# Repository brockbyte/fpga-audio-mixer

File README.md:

# FPGA Digital Audio Mixer with Network Control

## What is this project about?

I’ve been producing music for several years and was always searching for a control surface that offers a flexible number of faders and controls. Since I couldn’t find exactly what I had in mind, I decided to build one myself.
During discussions with another producer, the idea came up to not only design a control surface, but to integrate a basic mixer directly into the device. That was the moment I decided to move forward with a full FPGA-based design.
Initially, I considered combining an FPGA with a separate microcontroller to manage the physical control elements. However, because I wanted to display real-time information — such as peak meters — with fully deterministic timing, I chose a pure FPGA implementation in Verilog.
This approach provides completely predictable timing behavior. For example, the displays refresh every 20 ms — entirely independent of any other processes running on the chip. Additionally, the FPGA offers enough I/O pins to directly connect more complex control elements like rotary encoders. I can also instantiate as many I²C controllers as the available logic resources allow.

### Mixer Architecture

One of the key design questions was the type of input the mixer should support.
I initially experimented with implementing the Behringer UltraNet protocol (based on an existing open-source project). However, I wasn’t satisfied with the stability of the data transmission on my development board.
Since I had already worked extensively with FPGA-based networking in the past — and was interested in exploring DANTE/AES67 technologies — I decided to design the mixer around network-based audio streams.
While clock jitter still needs careful consideration, handling it within an FPGA environment feels more transparent and easier to debug compared to proprietary protocols. Thanks to DANTE’s AES67 mode, the mixer integrates seamlessly with professional studio equipment.
At the same time, you don’t need expensive studio hardware to experiment with the system. There are several open-source AES67-compatible software tools available, making it accessible for development and testing.

### Project Overview

This project combines:
* A fully FPGA-based digital mixer
* Motorized faders and hardware controls
* Deterministic display updates and metering
* Network-based audio input (AES67-compatible)
* Flexible and scalable architecture

If you have any questions, feel free to reach out.
I also have a limited number of PCBs from the first production run available — in case you’d like to start soldering and build your own board.

**Table of Contents**
1. [Hardware Components](#hardware-components)
2. [System Overview](#system-overview)
3. [Architecture & Clock Domains](#architecture--clock-domains)

---

## Hardware Components

### Intel Cyclone 10 LP Development Board
The heart of the digital audio mixer is the Intel Cyclone 10 LP Evaluation Kit. This platform was selected as it provides a few significant benefits:

* sufficient large Cyclone 10 FPGA to implement network, audio and control functionality
* ingegrated 1G network port
* a large number of input / output pins
* on-board JTAG programmer and debugger
* acceptable price of around 100 EUR

### Control Board Bill of Materials (BOM)
The custom control surface communicates with the FPGA via a 40-pin GPIO ribbon cable and some more dedicated cables. The board has been designed with KiCad. For the first production batch, I did not take special care of analog signal routing for the ADC for the faders and touch. It works in my environment, however, for the next production run maybe someone with more experience on that could give some hints on the layout ;-)

For this design I selected 60 mm faders, as the board would have become too big with the 100 mm faders. I tried to avoid using SMD components in this early design phase to make manual corrections easy and only used pre-built modules that can be either stacked into sockets or soldered directly.

| Component | Part Number | Quantity | Function |
| :--- | :--- | :--- | :--- |
| **Motorized Faders** | **MF60T** | 8 | Behringer 60 mm standard 10k Linear |
| **Motor Drivers** | **TB6612** (Dual) | 4 | PWM-based motor driver for 8 fader motors |
| **Touch Sensor** | **MPR121** | 1 | Capacitive touch detection |
| **I2C Multiplexer** | **PCA9548** | 1 | Individual addressing for the 8 OLED displays |
| **OLED Displays** | **128x64 I2C** | 8 | Per-channel labels, Pan, and Peak Meters |
| **Port Expander** | **MCP23017** | 1 | Driving LEDs for Mute and Solo buttons |
| **Rotary Encoders** | **STEC12** | 8 | Pan control |
| **Connectors** | 40-pin IDC | 1 | Main interface to the FPGA development board |

---

## Network & Protocol Implementation

### AES67 & SDP
The mixer adheres to the **AES67 standard** for interoperability with professional Audio-over-IP (AoIP) ecosystems.

* **Fixed Parameters:** To maintain a pure hardware implementation, the stream is fixed at **48 kHz, 24-bit (L24 format)**.
* **Session Description Protocol (SDP):** A static SDP file is provided to define multicast addresses, ports, and payload types, allowing external receivers to subscribe to the mixer's output.

### Multicast & Switch Strategy
The system utilizes **IP Multicast** for efficient one-to-many audio distribution.

* **Simplified Implementation:** To reduce FPGA gate usage and complexity, the design **does not implement IGMP Join/Leave messages**. 
* **Network Requirement:** Because the hardware does not actively "announce" its presence via IGMP, the network switch must be configured for **Static Multicast** or allowed to flood the multicast traffic to the target ports. This trade-off allows for a significantly leaner RTL network stack and is absolutely sufficient for hoem or small studio environments.

### Network Configuration

Since this project implements a pure hardware UDP/IP stack, IP addresses are currently **hardcoded** in the RTL to ensure maximum performance and zero-config startup.

**Current Default Settings**
My DANTE network has the IP range 192.168.1.0/24. By default, the project is configured with the following static IP addresses:

| Parameter | Default Value | Description |
| :--- | :--- | :--- |
| **Mixer IP Address** | `192.168.1.128` | The static IP of the FPGA board |
| **Frontend Server IP Address** | `192.168.1.100` | The static IP of the python server that receives the status messages |
| **Subnet Mask** | `255.255.255.0` | Standard Class C subnet |
| **Gateway** | `192.168.1.1` | Default network gateway |
| **Multicast Group** | `239.69.1.2` | Destination for AES67 RTP audio streams |
| **RTP Port** | `5004` | Standard port for RTP audio |

**How to Change IP Addresses**
If your network environment uses a different subnet, you must update the addresses in the source code before recompiling in Quartus.

1. **FPGA RTL (Hardware):**
   Look for the hexadecimal representation of the IP:
   * Example: `32'hC0A80164` corresponds to `192.168.1.100`.
   
2. **Web Frontend:**
   Open the `frontend/config.js` (or similar configuration file in the `/frontend` directory).
   Update the `MIXER_IP` constant to match the address set in the FPGA:
   ```javascript
   const MIXER_IP = "192.168.1.128";

## System Overview

### Board

The following figure shows the elements on the custom mixer control baord. The control board is powered with 3,3V from the FPGA board and has an additional 9V power supply for the fader motors.

**Board Picture**

#### 1. Fader

Each channel features a motorized linear fader at the bottom of the panel.
It is used to control the channel level (volume). The motorization allows the fader to move automatically to reflect external control from the web interface.

#### 2. Mute / Solo Buttons

Above each fader there are illuminated push buttons:

- Mute: Instantly silences the corresponding channel when activated.
- Solo: Isolates the channel for monitoring, muting all other channels depending on the solo mode.

The LED backlighting provides immediate visual feedback about the current state (active/inactive).

#### 3. OLED Display

Each channel has a small OLED display positioned above the buttons.
The display shows channel-related information, such as:

- Channel or track name
- Pan position (L / C / R)
- Pre-fader input meter

#### 4. Pan Rotary Knob

At the top of each channel strip there is a rotary encoder (pan knob).
It is used to adjust the stereo pan position, placing the signal anywhere between the left and right output channels.
Because it is an encoder rather than a simple potentiometer, it supports precise digital control and remote control.

#### 5. Rotary connector

Initially I intended to use port extenders for the rotary encoders. 
However, during development it turned out that the extenders are too slow for quick movements of the encoders and debouncing was hard.
So I changed the setup and connected the encoders directly to the FPGA, which allows flexible debounce and stable and quick detection. 

#### 6. MCP23017 port extenders

The port extenders are used for the LED buttons.

#### 7. Main PCB connector

A 40 pin ribbon cable connects the board to the FPGA system.

#### 8. TB6612 motor drivers

In total 4 motor drivers are on the board for the 8 fader channels.

#### 9. MPR121 capacitative touch

The touch IC detects if a fader knob is touched and motor control is disabled for this channel.

#### 10. PCA9548 I2C multiplexer

The I2C multiplexer is used for the 8 OLED displays.

### Web frontend

The web frontend implements the same controls that are available on the local control interface.
It can sends updates to the mixer and receives regular status updates from the FPGA main mixer system.

### Core Subsystems

**Audio Subsystem**
- 16-channel input mixer with independent gain, pan, mute, and solo per channel (current demo system uses 8 channels)
- 2-channel stereo output (summed from 16 inputs with pan law)
- AES67 RTP network audio receive (UDP port 5004)
- Optional network audio transmit capability
- Adaptive jitter buffer with clock drift compensation
- Peak detection and hold/decay metering

**Timing Subsystem**
- IEEE 1588 (PTP v2) clock synchronization to master device
- Automatic 48 kHz audio clock generation locked to master timing
- PI servo controller for precise frequency tracking
- Anti-windup and wrap-safe counter management

**Network & Telemetry**
- UDP status packet streaming (port 7880) with complete mixer state snapshot
- Packet includes peaks, pan, gain, mute/solo, channel names, jitter buffer status
- Optional SDP (Session Description Protocol) announcements for device discovery

### Included Libraries

#### verilog-ethernet

The project relies on the UDP / Ethernet implementation made by Alex Forencich.
It is available here: https://github.com/alexforencich/verilog-ethernet

#### verilog-i2c

For the I2C communication, the i2c-master from verilog-12c by Alex Forencich is used.
It is available here: https://github.com/alexforencich/verilog-i2c/tree/master

#### spdif

A working SPDIF transmitter, which I have tried with this project can be found here:
https://ackspace.nl/wiki/SP/DIF_transmitter_project

---

## Architecture & Clock Domains

### Multi-Clock System Design

The FPGA uses three synchronized but independent clock domains:

```
┌─────────────────────────────────────────────────────────────┐
│                    Ethernet PHY (1000BASE-T)                │
│                         RGMII Interface                     │
└────────────────────────────┬────────────────────────────────┘
                             │
        ┌────────────────────┼────────────────────┐
        │                    │                    │
        ↓                    ↓                    ↓
    125 MHz             50 MHz Primary       12.288 MHz SPDIF
  Ethernet Clock      Control Clock          Output Clock
    (Network)          (Mixed Signal)         (Audio Output)
        │                    │                    │
        ├─ UDP/IP Stack      ├─ Audio Mixer      └─ SPDIF Output
        ├─ RTP Parsing       ├─ Fader Control       Encoding
        ├─ PTP Reception     ├─ Button Input
        ├─ Packet Routing    ├─ OLED Display
        └─ Network Timing    └─ Status Capture
                             
```

### Clock Domain Crossing Strategy

**Safe data transfer between domains:**

| Crossing | Method | Module | Purpose |
|---------|--------|--------|---------|
| 125 MHz → 50 MHz | Async FIFO | `axis_udp_payload_async_fifo.v` | UDP packet payload buffering |
| 50 MHz → 125 MHz | Async FIFO | `tx_asyncfifo10b_axi.v` | Network transmit path |
| 48 kHz ↔ 50 MHz | Custom FIFO | `jitter_buffer_dcfifo_resampler.v` | Audio buffering with resampling |

### System Hierarchy

```
fpga.v (Top-Level Wrapper)
├── PLL (generates 50M, 12.288M from 125M input)
├── Reset Synchronizers (async reset → sync reset per domain)
│
└── fpga_core.v (Main Integration)
    │
    ├── Ethernet MAC Layer (verilog-ethernet library)
    │   ├── RGMII RX/TX (125 MHz physical interface)
    │   ├── Ethernet MAC (address filtering, CRC)
    │   └── ARP and basic management
    │
    ├── IP & UDP Stack (verilog-ethernet library)
    │   ├── IPv4 header processing
    │   ├── UDP demultiplexer (4 ports: 319, 320, 5004, 7880)
    │   ├── UDP transmit aggregator
    │   └── Checksum generation
    │
    ├── PTP Client Implementation
    │   ├── ptp_client_stream_50m: Sync message reception
    │   ├── ptp_v2_sync_follow_parser_stream: Timestamp extraction
    │   ├── ptp_client_servo_light_wrapsafe_dbg: PI servo (KP=0.5, KI=0.001)
    │   └── ptp_timebase_slew: 48 kHz generation with slew-rate limiting
    │
    ├── Audio Processing Path (50 MHz → 48 kHz)
    │   ├── aes67_rtp_rx_fifo: UDP → RTP packet parsing
    │   ├── jitter_buffer_dcfifo_resampler: Adaptive buffering + resampling
    │   ├── mixer_16x2_q14_pipelined_patched: 3-stage pipelined 16×2 mixer
    │   ├── pan_gain_coeff_calc16_rom: Pan law coefficient lookup (256-entry ROM)
    │   └── aes67_tx_stream2_from_fifo48_lr: RTP packet generation (optional output)
    │
    ├── Control Interface Subsystem (50 MHz)
    │   │
    │   ├── Fader Motor Control
    │   │   ├── mcp3008_rr: 8-channel SPI ADC round-robin scanner (100 kHz SPI)
    │   │   ├── fader_channel_logic_10b_int: Per-channel PI servo (Kp=0.5, Ki=0.03)
    │   │   └── mixer_top_8ch: Orchestrator (PWM @ 20 kHz to TB6612 drivers)
    │   │
    │   ├── Button Input (16 buttons via 2× MCP23017)
    │   │   ├── mcp23017_dual_ctrl: I2C GPIO read (2 ms poll interval)
    │   │   └── mcp_buttons_toggle_plus_solo: Debounce + toggle/solo logic
    │   │
    │   ├── Touch Sensing (8 sensors via MPR121)
    │   │   └── mpr121_poll8_simplified-v2: I2C polling (1 ms interval)
    │   │
    │   └── Rotary Encoders (8 channels, quadrature decoding)
    │       └── rotary8_stec12e08_debounced: Quadrature phase detection
    │
    ├── Display & Monitoring System (50 MHz)
    │   ├── oled_mixer8_ssd1306_tca9548_axis: 8-display controller (20 ms refresh)
    │   │   ├── TCA9548 I2C multiplexer (1-of-8 channel selection)
    │   │   ├── Name
    │   │   ├── Peak meter rendering (12 segments, hold/decay)
    │   │   └── Pan indicator visualization
    │   │
    │   ├── name_ram_1w2r: 1-write, 2-read BRAM (256×8, dual independent reads)
    │   ├── name_dp_ram: Dual-port BRAM building block
    │   └── font7x12_pages_bram: Font storage (1536 bytes, M9K BRAM)
    │
    ├── Status & Telemetry
    │   ├── udp_status_tx_bram: Status capture (424-byte snapshot per cycle)
    │   ├── sdp_udp_stream_from_rom: SDP announcer (periodic broadcast)
    │   └── udp_debug_tx: Optional debug streaming
    │
    ├── Network Routing
    │   ├── udp_port_demux_4: 4-way input routing (fixed priority)
    │   └── udp_tx_mux4_from_streams_clean: 4-way output arbitration (priority 0>1>2>3)
    │
    └── Clock Domain FIFOs
        ├── axis_udp_payload_async_fifo: 8-bit, 512 deep (125M→50M crossing)
        ├── tx_asyncfifo10b_axi: 10-bit, 4096 deep (50M→125M crossing)
        ├── custom_async_fifo: 48-bit, 512 deep (general purpose)
        ├── net_async_fifo_10b: 10-bit, 4096 deep (packet format {start,end,data})
        ├── aes67sendfifo: 50-bit, 256 deep (audio tx buffering)
        └── sdebug_async_fifo: 8-bit, 4096 deep (debug streaming)
```

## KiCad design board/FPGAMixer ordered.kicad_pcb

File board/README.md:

# Board Assembly Notes

## ⚠️ Hardware Error - Manual Soldering Required

There is an error in the schematic and board layout. **PIN 36 of the 40 pin connector and PIN 13 of the MCP3008 IC should be connected**, but due to a net name mismatch in the schematic, they are not.

**You need to solder a connection manually between these two pins.**

## Alternative connections for rotary encoders

I first tried to connect the rotary encoders via the MCP I/O expander. However, that turned out to be not working properly due to a lot issues with switch bouncing, as the MCP were not fast enough for rotating the knobs quickly. So, I connected the rotary encoders also directly to the FPGA. Luckily, the Intel Dev board had a lot of pins left I could use. Performing all the debounce stuff inside the FPGA worked really well and also the FPGA was fast enough for handling also quick rotations.

If you build the system, here is a picture of how I connected the rotary pins to the FPGA. Instead of soldering the MCP ICs, I just soldered headers:

And on the FPGA side it looks like this:

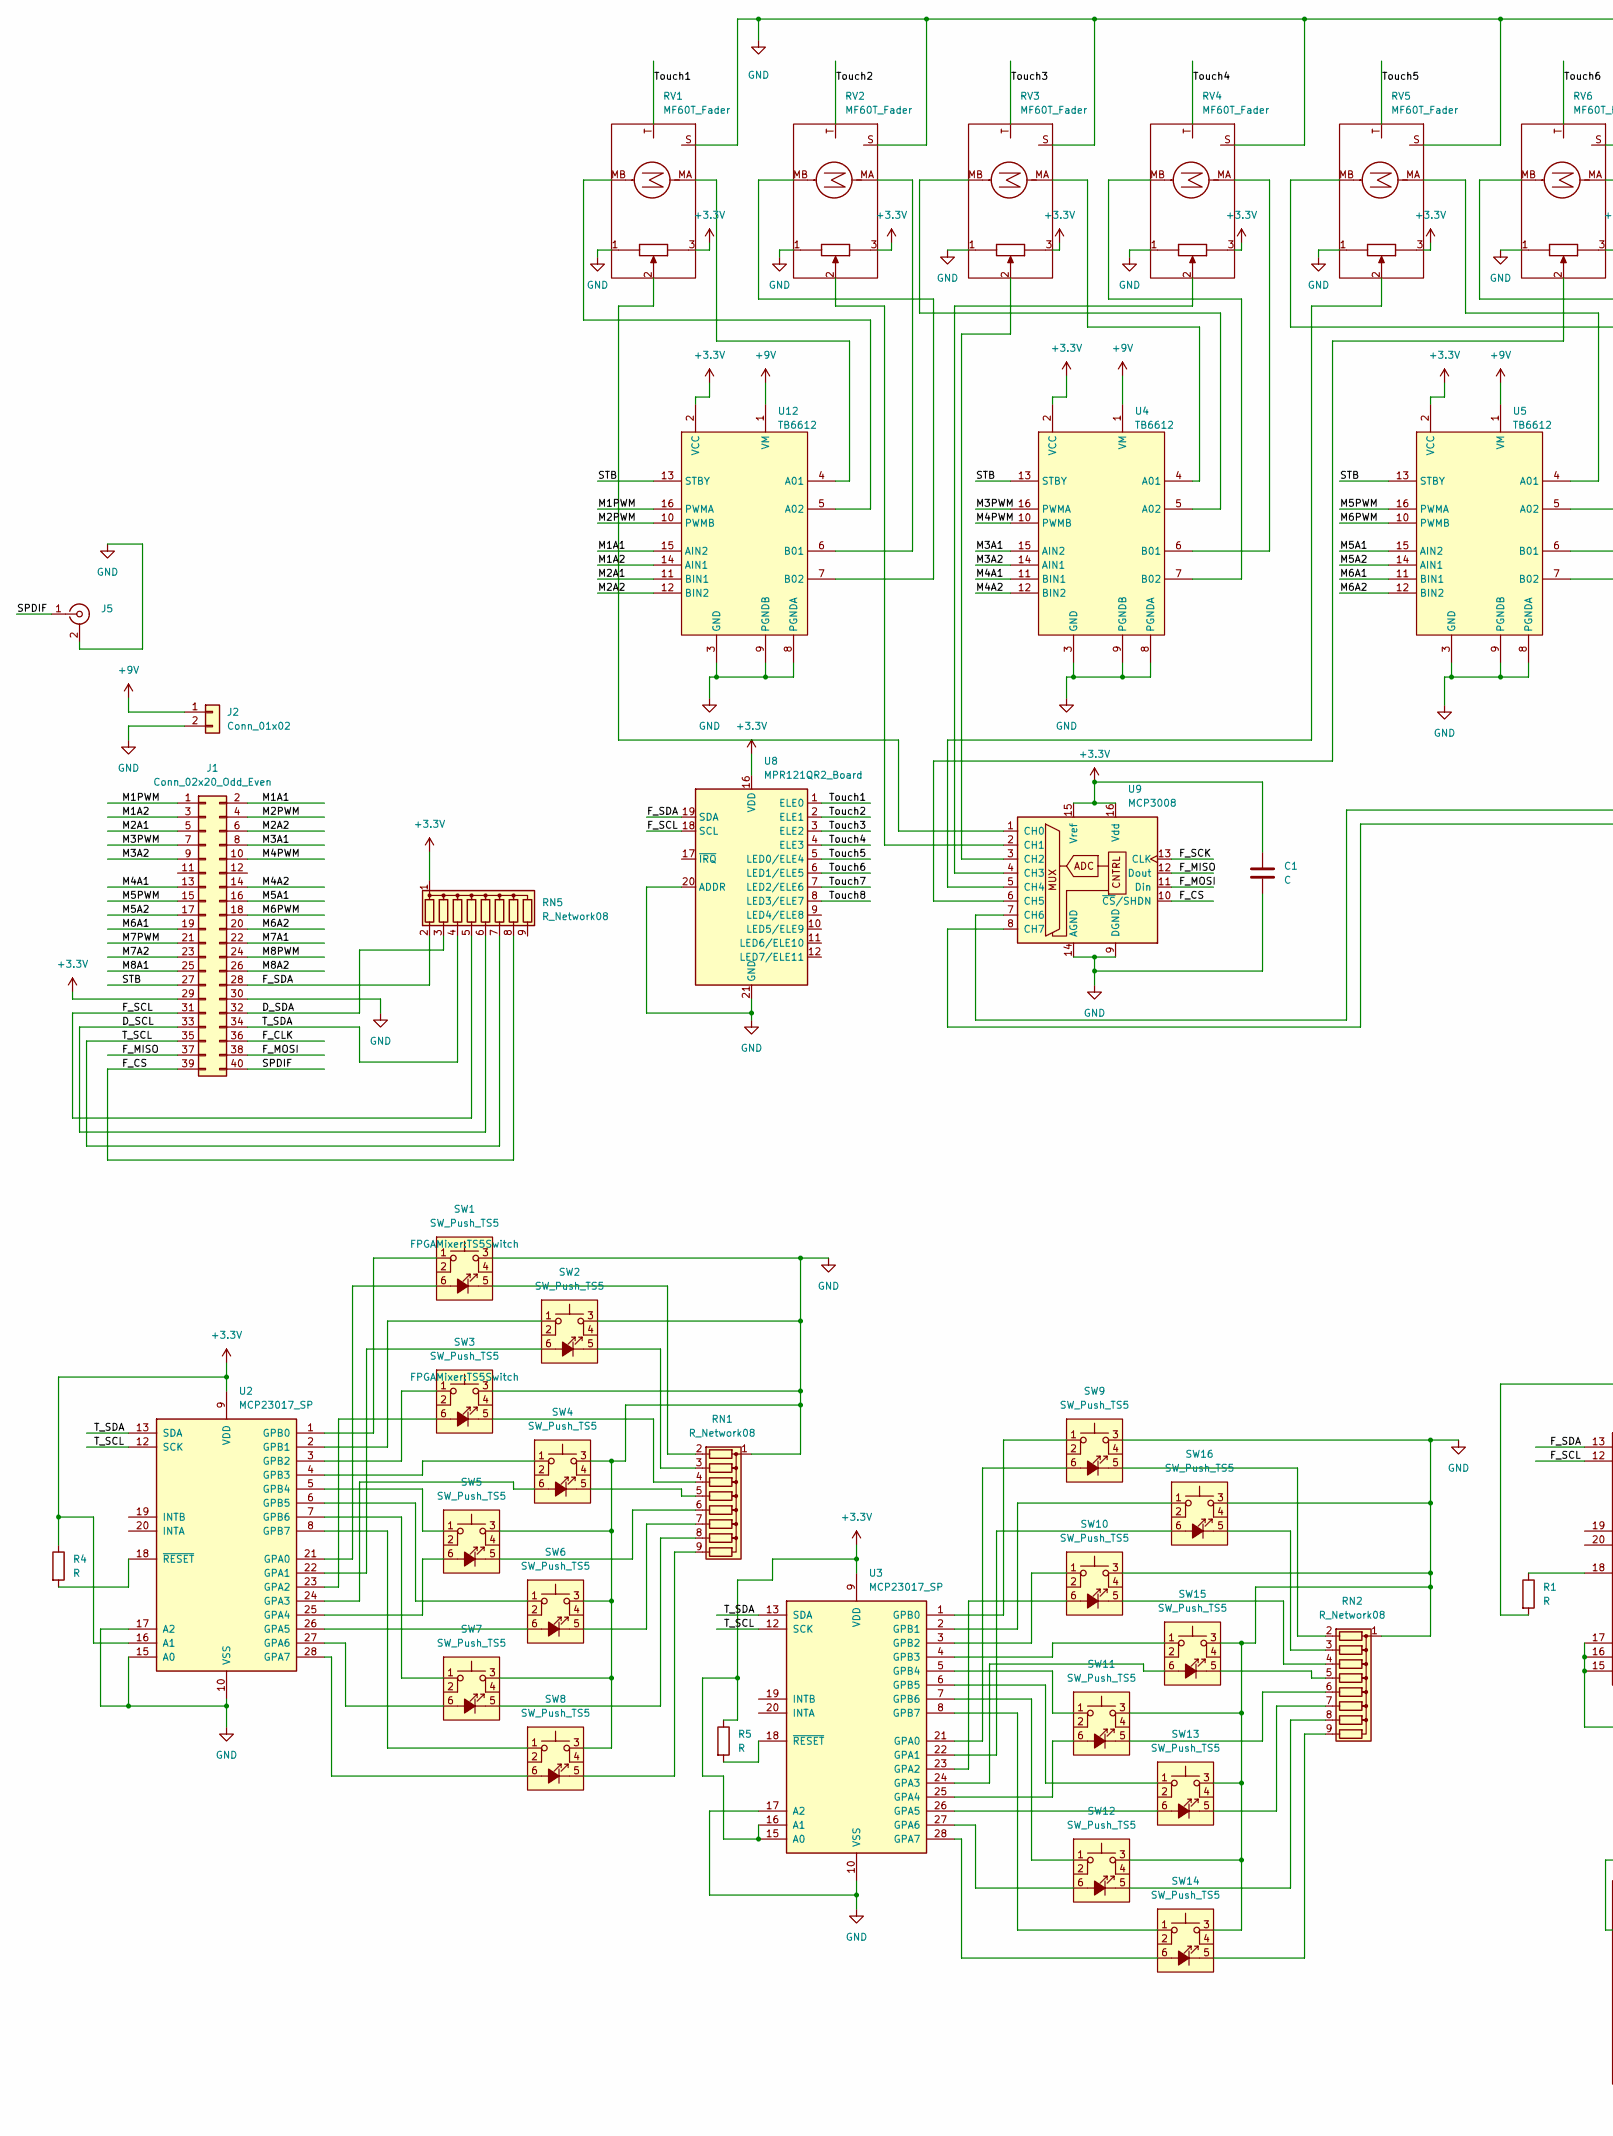
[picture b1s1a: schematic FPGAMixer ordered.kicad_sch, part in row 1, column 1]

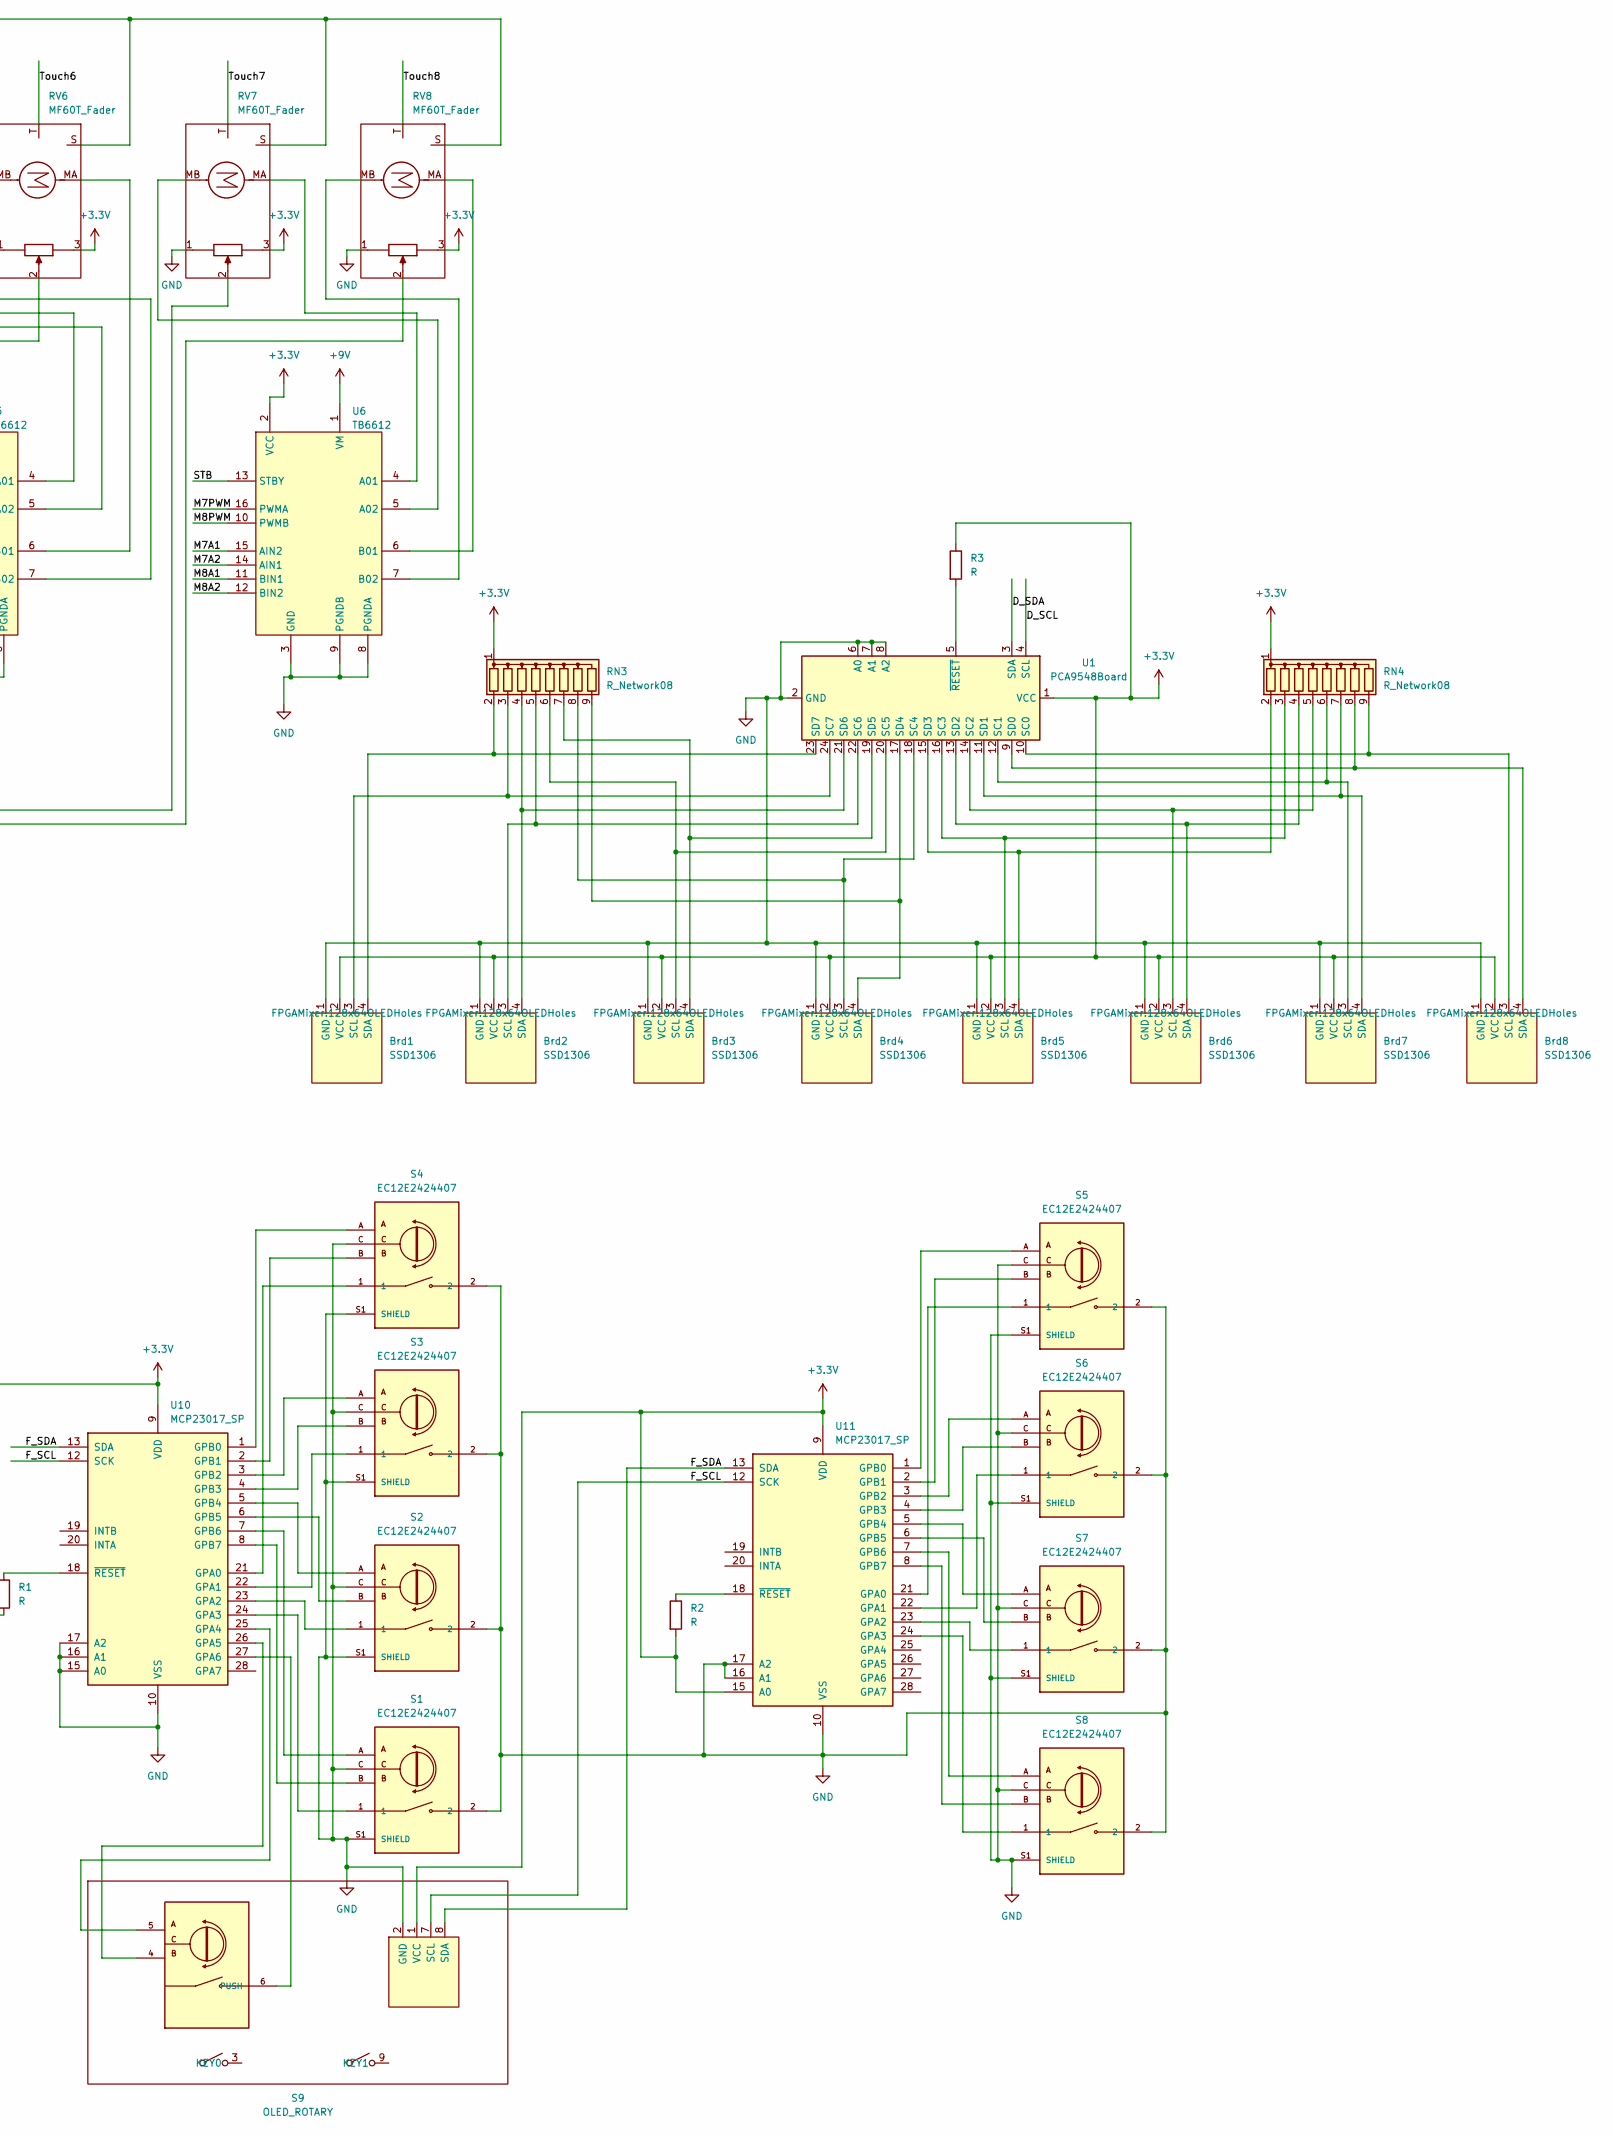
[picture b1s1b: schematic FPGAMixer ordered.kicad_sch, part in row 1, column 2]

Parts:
Brd1, Brd2, Brd3, Brd4, Brd5, Brd6, Brd7, Brd8: SSD1306; 128x64OLEDHoles
C1: C; C_Disc_D5.0mm_W2.5mm_P5.00mm
J1: Conn_02x20_Odd_Even; PinHeader_2x20_P2.54mm_Vertical
J2: Conn_01x02; PinHeader_1x02_P2.54mm_Vertical
J5: Conn_Coaxial; RCA_Jack
R1, R2, R3, R4, R5: R; R_Axial_DIN0207_L6.3mm_D2.5mm_P10.16mm_Horizontal
RN1, RN2, RN3, RN4, RN5: R_Network08; R_Array_SIP9
RV1, RV2, RV3, RV4, RV5, RV6, RV7, RV8: MF60T_Fader; MFT60
S1, S2, S3, S4, S5, S6, S7, S8: EC12E2424407; ALPS_EC12E2424407; PARTREV N/A
S9: OLED_ROTARY; OLEDwEC11; PARTREV N/A
SW1, SW2, SW3, SW4, SW5, SW6, SW7, SW8, SW9, SW10, SW11, SW12, SW13, SW14, SW15, SW16: SW_Push_TS5; TS5Switch
U1: PCA9548Board; HW-617
U2, U3, U10, U11: MCP23017_SP; DIP-28_W7.62mm
U4, U5, U6, U12: TB6612; MODULE_ROB-14450
U8: MPR121QR2_Board; MPR121_Board
U9: MCP3008; DIP-16_W7.62mm

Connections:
+3.3V: Brd1.2 (VCC), Brd2.2 (VCC), Brd3.2 (VCC), Brd4.2 (VCC), Brd5.2 (VCC), Brd6.2 (VCC), Brd7.2 (VCC), Brd8.2 (VCC), C1.1, J1.29, R1.2, R2.2, R3.1, R4.1, R5.1, RN3.1 (common), RN4.1 (common), RN5.1 (common), RV1.3 (VCC), RV2.3 (VCC), RV3.3 (VCC), RV4.3 (VCC), RV5.3 (VCC), RV6.3 (VCC), RV7.3 (VCC), RV8.3 (VCC), S9.1 (VCC), U1.1 (VCC), U2.9 (VDD), U2.16 (A1), U3.9 (VDD), U3.15 (A0), U3.16 (A1), U4.2 (VCC), U5.2 (VCC), U6.2 (VCC), U8.16 (VDD), U9.15 (Vref), U9.16 (Vdd), U10.9 (VDD), U11.9 (VDD), U11.15 (A0), U12.2 (VCC)
+9V: J2.1, U4.1 (VM), U5.1 (VM), U6.1 (VM), U12.1 (VM)
/D_SCL: J1.33, RN5.6 (R5), U1.4 (SCL)
/D_SDA: J1.32, RN5.3 (R2), U1.3 (SDA)
/F_CLK: J1.36
/F_CS: J1.39, RN5.8 (R7), U9.10 (~CS/SHDN)
/F_MISO: J1.37, U9.12 (Dout)
/F_MOSI: J1.38, U9.11 (Din)
/F_SCK: U9.13 (CLK)
/F_SCL: J1.31, RN5.5 (R4), S9.7 (SCL), U8.18 (SCL), U10.12 (SCK), U11.12 (SCK)
/F_SDA: J1.28, RN5.2 (R1), S9.8 (SDA), U8.19 (SDA), U10.13 (SDA), U11.13 (SDA)
/M1A1: J1.2, U12.15 (AIN2)
/M1A2: J1.3, U12.14 (AIN1)
/M1PWM: J1.1, U12.16 (PWMA)
/M2A1: J1.5, U12.11 (BIN1)
/M2A2: J1.6, U12.12 (BIN2)
/M2PWM: J1.4, U12.10 (PWMB)
/M3A1: J1.8, U4.15 (AIN2)
/M3A2: J1.9, U4.14 (AIN1)
/M3PWM: J1.7, U4.16 (PWMA)
/M4A1: J1.13, U4.11 (BIN1)
/M4A2: J1.14, U4.12 (BIN2)
/M4PWM: J1.10, U4.10 (PWMB)
/M5A1: J1.16, U5.15 (AIN2)
/M5A2: J1.17, U5.14 (AIN1)
/M5PWM: J1.15, U5.16 (PWMA)
/M6A1: J1.19, U5.11 (BIN1)
/M6A2: J1.20, U5.12 (BIN2)
/M6PWM: J1.18, U5.10 (PWMB)
/M7A1: J1.22, U6.15 (AIN2)
/M7A2: J1.23, U6.14 (AIN1)
/M7PWM: J1.21, U6.16 (PWMA)
/M8A1: J1.25, U6.11 (BIN1)
/M8A2: J1.26, U6.12 (BIN2)
/M8PWM: J1.24, U6.10 (PWMB)
/SPDIF: J1.40, J5.1 (In)
/STB: J1.27, U4.13 (STBY), U5.13 (STBY), U6.13 (STBY), U12.13 (STBY)
/T_SCL: J1.35, RN5.7 (R6), U2.12 (SCK), U3.12 (SCK)
/T_SDA: J1.34, RN5.4 (R3), U2.13 (SDA), U3.13 (SDA)
/Touch1: RV1.T (Touch), U8.1 (ELE0)
/Touch2: RV2.T (Touch), U8.2 (ELE1)
/Touch3: RV3.T (Touch), U8.3 (ELE2)
/Touch4: RV4.T (Touch), U8.4 (ELE3)
/Touch5: RV5.T (Touch), U8.5 (LED0/ELE4)
/Touch6: RV6.T (Touch), U8.6 (LED1/ELE5)
/Touch7: RV7.T (Touch), U8.7 (LED2/ELE6)
/Touch8: RV8.T (Touch), U8.8 (LED3/ELE7)
GND: Brd1.1 (GND), Brd2.1 (GND), Brd3.1 (GND), Brd4.1 (GND), Brd5.1 (GND), Brd6.1 (GND), Brd7.1 (GND), Brd8.1 (GND), C1.2, J1.30, J2.2, J5.2 (Ext), RN1.1 (common), RN2.1 (common), RV1.1 (GND), RV1.S, RV2.1 (GND), RV2.S, RV3.1 (GND), RV3.S, RV4.1 (GND), RV4.S, RV5.1 (GND), RV5.S, RV6.1 (GND), RV6.S, RV7.1 (GND), RV7.S, RV8.1 (GND), RV8.S, S1.2, S1.C, S1.S1 (SHIELD), S1.S2 (SHIELD), S2.2, S2.C, S2.S1 (SHIELD), S2.S2 (SHIELD), S3.2, S3.C, S3.S1 (SHIELD), S3.S2 (SHIELD), S4.2, S4.C, S4.S1 (SHIELD), S4.S2 (SHIELD), S5.2, S5.C, S5.S1 (SHIELD), S5.S2 (SHIELD), S6.2, S6.C, S6.S1 (SHIELD), S6.S2 (SHIELD), S7.2, S7.C, S7.S1 (SHIELD), S7.S2 (SHIELD), S8.2, S8.C, S8.S1 (SHIELD), S8.S2 (SHIELD), S9.2 (GND), SW1.3, SW2.3, SW3.3, SW4.3, SW5.3, SW6.3, SW7.3, SW8.3, SW9.3, SW10.3, SW11.3, SW12.3, SW13.3, SW14.3, SW15.3, SW16.3, U1.2 (GND), U1.6 (A0), U1.7 (A1), U1.8 (A2), U2.10 (VSS), U2.15 (A0), U2.17 (A2), U3.10 (VSS), U3.17 (A2), U4.3 (GND), U4.8 (PGNDA), U4.9 (PGNDB), U5.3 (GND), U5.8 (PGNDA), U5.9 (PGNDB), U6.3 (GND), U6.8 (PGNDA), U6.9 (PGNDB), U8.20 (ADDR), U8.21 (GND), U9.9 (DGND), U9.14 (AGND), U10.10 (VSS), U10.15 (A0), U10.16 (A1), U10.17 (A2), U11.10 (VSS), U11.16 (A1), U11.17 (A2), U12.3 (GND), U12.8 (PGNDA), U12.9 (PGNDB)
unnamed: Brd1.3 (SCL), RN3.3 (R2), U1.24 (SC7)
unnamed: Brd1.4 (SDA), RN3.2 (R1), U1.23 (SD7)
unnamed: Brd2.3 (SCL), RN3.5 (R4), U1.22 (SC6)
unnamed: Brd2.4 (SDA), RN3.4 (R3), U1.21 (SD6)
unnamed: Brd3.3 (SCL), RN3.6 (R5), U1.20 (SC5)
unnamed: Brd3.4 (SDA), RN3.7 (R6), U1.19 (SD5)
unnamed: Brd4.3 (SCL), RN3.8 (R7), U1.18 (SC4)
unnamed: Brd4.4 (SDA), RN3.9 (R8), U1.17 (SD4)
unnamed: Brd5.3 (SCL), RN4.3 (R2), U1.16 (SC3)
unnamed: Brd5.4 (SDA), RN4.2 (R1), U1.15 (SD3)
unnamed: Brd6.3 (SCL), RN4.5 (R4), U1.14 (SC2)
unnamed: Brd6.4 (SDA), RN4.4 (R3), U1.13 (SD2)
unnamed: Brd7.3 (SCL), RN4.6 (R5), U1.12 (SC1)
unnamed: Brd7.4 (SDA), RN4.7 (R6), U1.11 (SD1)
unnamed: Brd8.3 (SCL), RN4.9 (R8), U1.10 (SC0)
unnamed: Brd8.4 (SDA), RN4.8 (R7), U1.9 (SD0)
unnamed: RN1.2 (R1), SW1.5 (K)
unnamed: RN1.3 (R2), SW2.5 (K)
unnamed: RN1.4 (R3), SW3.5 (K)
unnamed: RN1.5 (R4), SW4.5 (K)
unnamed: RN1.6 (R5), SW5.5 (K)
unnamed: RN1.7 (R6), SW6.5 (K)
unnamed: RN1.8 (R7), SW7.5 (K)
unnamed: RN1.9 (R8), SW8.5 (K)
unnamed: RN2.2 (R1), SW9.5 (K)
unnamed: RN2.3 (R2), SW16.5 (K)
unnamed: RN2.4 (R3), SW10.5 (K)
unnamed: RN2.5 (R4), SW15.5 (K)
unnamed: RN2.6 (R5), SW11.5 (K)
unnamed: RN2.7 (R6), SW13.5 (K)
unnamed: RN2.8 (R7), SW12.5 (K)
unnamed: RN2.9 (R8), SW14.5 (K)
unnamed: S9.6 (PUSH), U10.27 (GPA6)
unnamed: SW1.6 (A), U2.21 (GPA0)
unnamed: SW2.6 (A), U2.22 (GPA1)
unnamed: SW3.6 (A), U2.23 (GPA2)
unnamed: SW4.6 (A), U2.24 (GPA3)
unnamed: SW5.6 (A), U2.25 (GPA4)
unnamed: SW6.6 (A), U2.26 (GPA5)
unnamed: SW7.6 (A), U2.27 (GPA6)
unnamed: SW8.6 (A), U2.28 (GPA7)
unnamed: SW9.6 (A), U3.21 (GPA0)
unnamed: SW10.6 (A), U3.23 (GPA2)
unnamed: SW11.6 (A), U3.25 (GPA4)
unnamed: SW12.6 (A), U3.27 (GPA6)
unnamed: SW13.6 (A), U3.26 (GPA5)
unnamed: SW14.6 (A), U3.28 (GPA7)
unnamed: SW15.6 (A), U3.24 (GPA3)
unnamed: SW16.6 (A), U3.22 (GPA1)
unnamed: R3.2, U1.5 (~RESET)
unnamed: SW1.1, U2.1 (GPB0)
unnamed: SW2.1, U2.2 (GPB1)
unnamed: SW3.1, U2.3 (GPB2)
unnamed: SW4.1, U2.4 (GPB3)
unnamed: SW5.1, U2.5 (GPB4)
unnamed: SW6.1, U2.6 (GPB5)
unnamed: SW7.1, U2.7 (GPB6)
unnamed: SW8.1, U2.8 (GPB7)
unnamed: R4.2, U2.18 (~RESET)
unnamed: SW9.1, U3.1 (GPB0)
unnamed: SW16.1, U3.2 (GPB1)
unnamed: SW10.1, U3.3 (GPB2)
unnamed: SW15.1, U3.4 (GPB3)
unnamed: SW11.1, U3.5 (GPB4)
unnamed: SW13.1, U3.6 (GPB5)
unnamed: SW12.1, U3.7 (GPB6)
unnamed: SW14.1, U3.8 (GPB7)
unnamed: R5.2, U3.18 (~RESET)
unnamed: RV3.MA, U4.4 (A01)
unnamed: RV3.MB, U4.5 (A02)
unnamed: RV4.MA, U4.6 (B01)
unnamed: RV4.MB, U4.7 (B02)
unnamed: RV5.MA, U5.4 (A01)
unnamed: RV5.MB, U5.5 (A02)
unnamed: RV6.MA, U5.6 (B01)
unnamed: RV6.MB, U5.7 (B02)
unnamed: RV7.MA, U6.4 (A01)
unnamed: RV7.MB, U6.5 (A02)
unnamed: RV8.MA, U6.6 (B01)
unnamed: RV8.MB, U6.7 (B02)
unnamed: RV1.2, U9.1 (CH0)
unnamed: RV2.2, U9.2 (CH1)
unnamed: RV3.2, U9.3 (CH2)
unnamed: RV4.2, U9.4 (CH3)
unnamed: RV5.2, U9.5 (CH4)
unnamed: RV6.2, U9.6 (CH5)
unnamed: RV7.2, U9.7 (CH6)
unnamed: RV8.2, U9.8 (CH7)
unnamed: S4.1, U10.21 (GPA0)
unnamed: S3.1, U10.22 (GPA1)
unnamed: S2.1, U10.23 (GPA2)
unnamed: S1.1, U10.24 (GPA3)
unnamed: S9.5, U10.25 (GPA4)
unnamed: S9.4, U10.26 (GPA5)
unnamed: S4.A, U10.1 (GPB0)
unnamed: S4.B, U10.2 (GPB1)
unnamed: S3.A, U10.3 (GPB2)
unnamed: S3.B, U10.4 (GPB3)
unnamed: S2.A, U10.5 (GPB4)
unnamed: S2.B, U10.6 (GPB5)
unnamed: S1.A, U10.7 (GPB6)
unnamed: S1.B, U10.8 (GPB7)
unnamed: R1.1, U10.18 (~RESET)
unnamed: S5.1, U11.21 (GPA0)
unnamed: S6.1, U11.22 (GPA1)
unnamed: S7.1, U11.23 (GPA2)
unnamed: S8.1, U11.24 (GPA3)
unnamed: S5.A, U11.1 (GPB0)
unnamed: S5.B, U11.2 (GPB1)
unnamed: S6.A, U11.3 (GPB2)
unnamed: S6.B, U11.4 (GPB3)
unnamed: S7.A, U11.5 (GPB4)
unnamed: S7.B, U11.6 (GPB5)
unnamed: S8.A, U11.7 (GPB6)
unnamed: S8.B, U11.8 (GPB7)
unnamed: R2.1, U11.18 (~RESET)
unnamed: RV1.MA, U12.4 (A01)
unnamed: RV1.MB, U12.5 (A02)
unnamed: RV2.MA, U12.6 (B01)
unnamed: RV2.MB, U12.7 (B02)

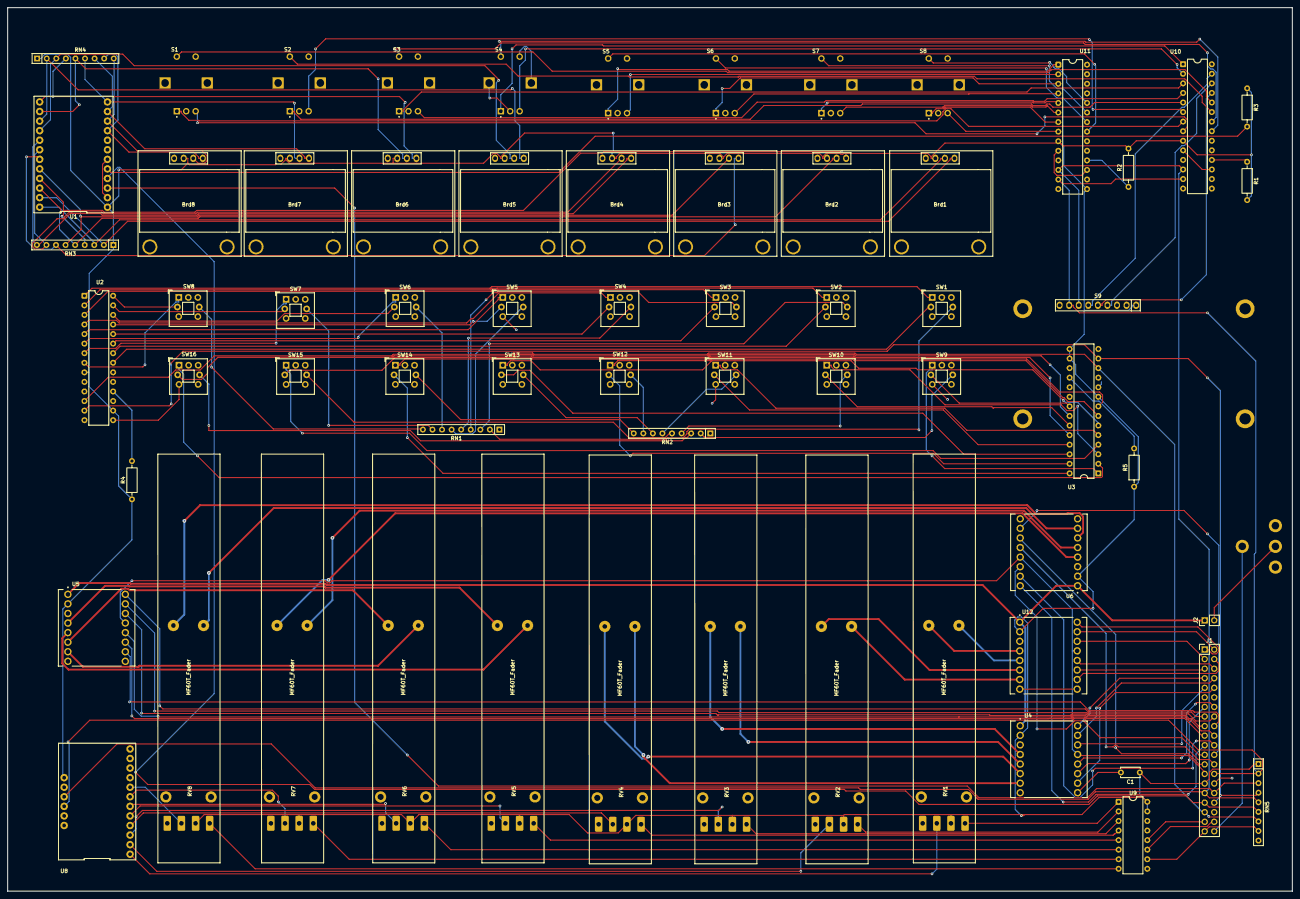
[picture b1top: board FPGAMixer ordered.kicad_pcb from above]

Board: 2 copper layers, 341.0 x 234.5 mm, 66 parts (0 on the bottom side), 166 nets.

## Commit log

2026-01-25 Update copyright year and owner in LICENSE file
2026-01-25 Initial commit: Add FPGA audio mixer project files
2026-02-04 Add files via upload
    Bilder vom Board
2026-02-04 Enhance README with hardware details and network config
    Added hardware components section and updated network configuration details in README.
2026-02-04 Change image reference in README for board layout
    Updated the image reference for the board correction.
2026-02-12 Enhance README with detailed project information
    Expanded project description with details about the FPGA digital audio mixer, its architecture, and components.
2026-02-12 Add detailed module specifications to README
    Added detailed specifications for various audio processing modules including audio mixer, jitter buffer, network timing, control interfaces, display system, and telemetry.
2026-02-12 Update Table of Contents in README.md
    Removed sections on Detailed Module Specifications, Signal Formats & Data Paths, and Configuration Parameters from the Table of Contents.
2026-05-23 Add files via upload
    Images for Rotary Encoder Connections
2026-05-23 Add info for rotary connection
2026-05-23 Create LICENSE
    Switch to CERN-OHL-P
